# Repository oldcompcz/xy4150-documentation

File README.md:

# xy4150-documentation
Technical documentation about plotter XY 4150

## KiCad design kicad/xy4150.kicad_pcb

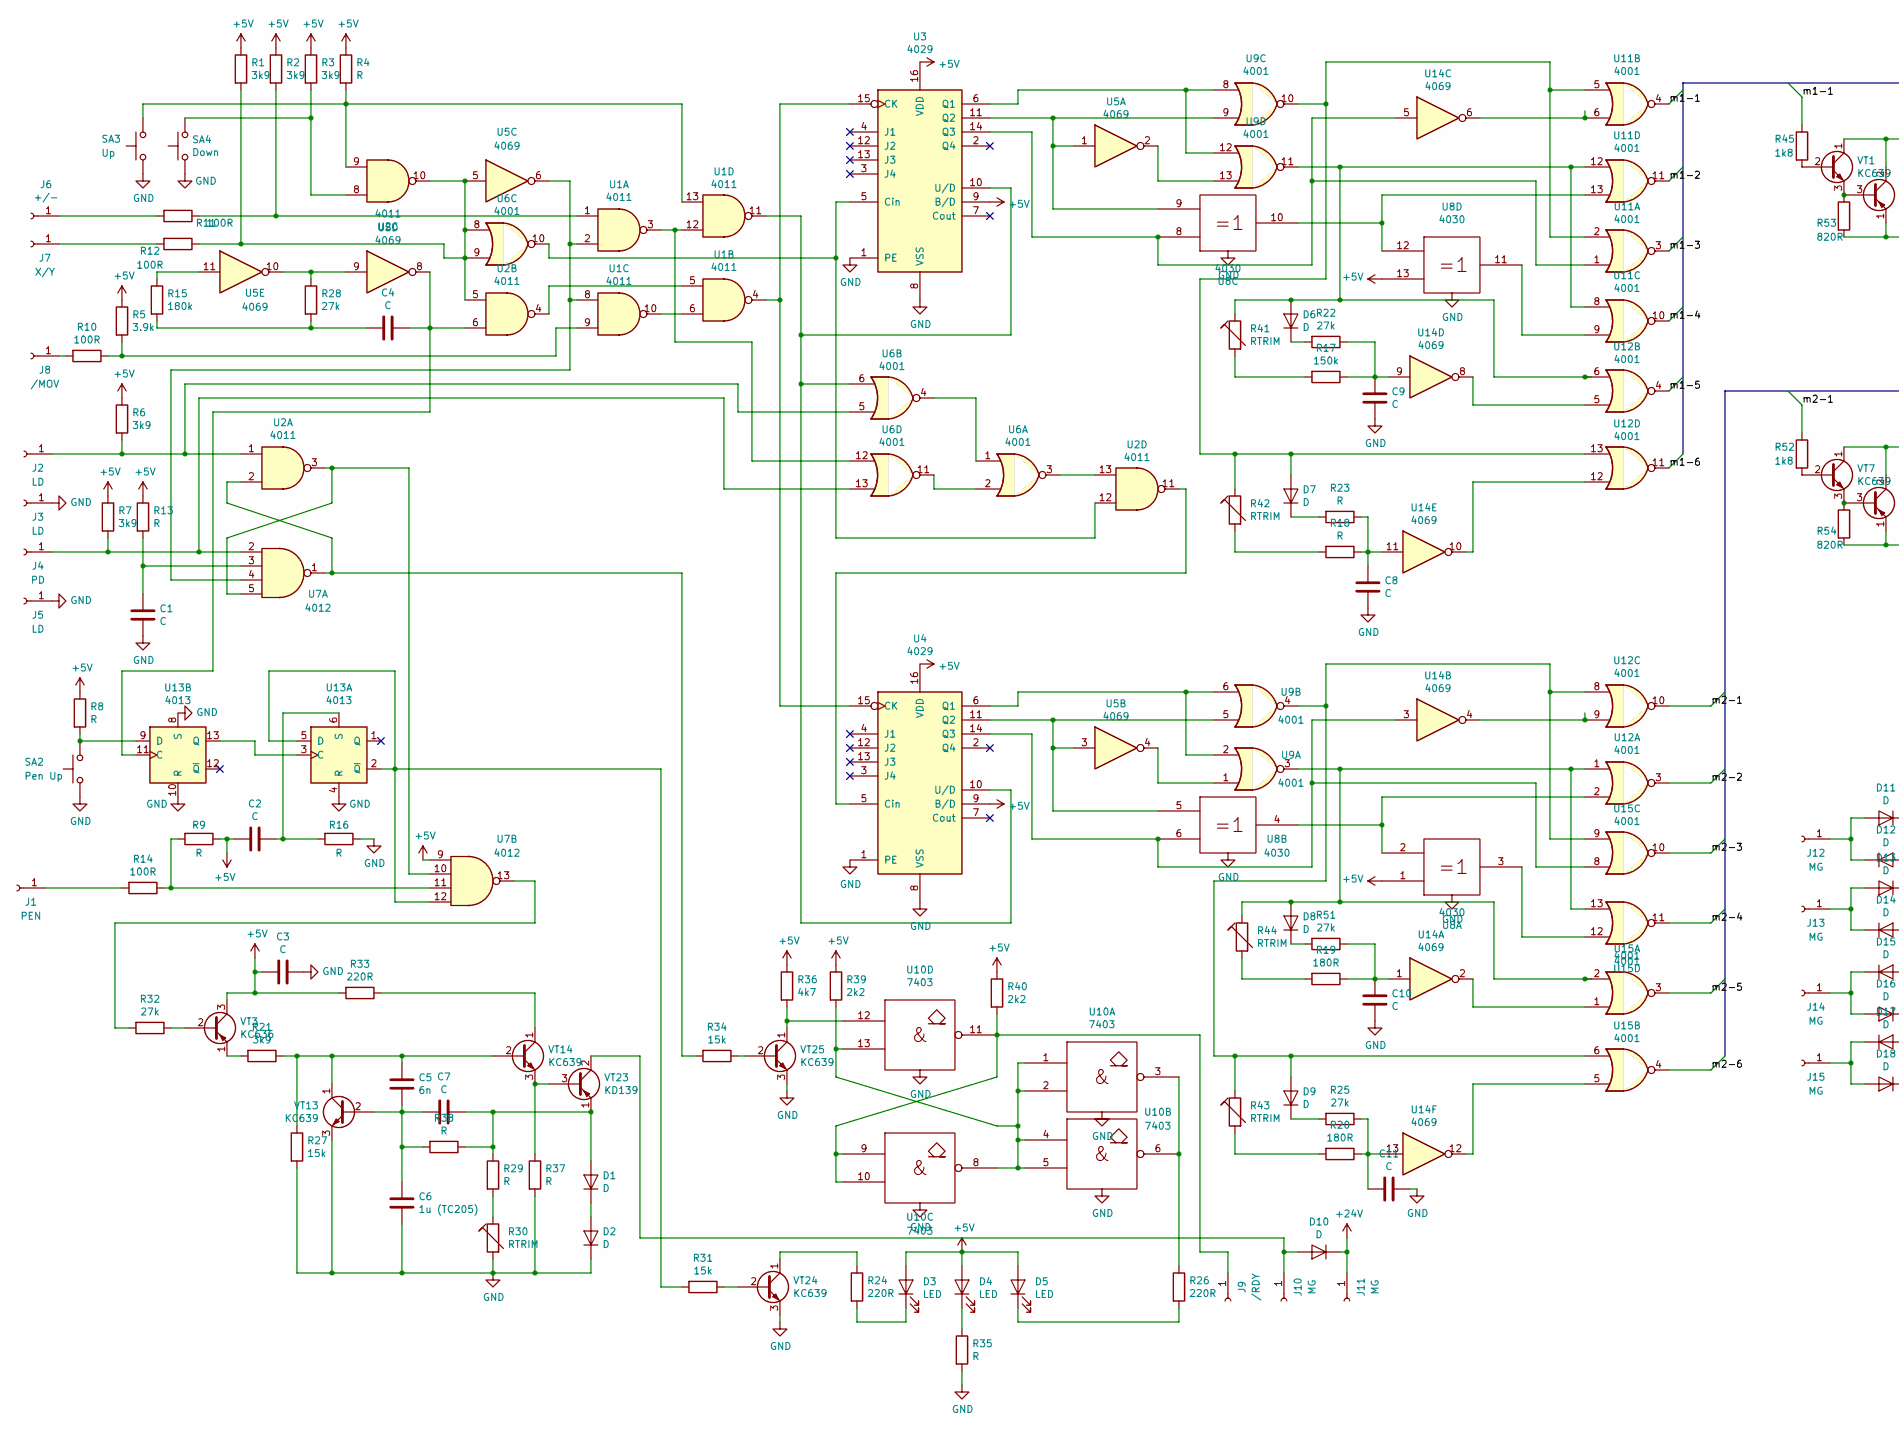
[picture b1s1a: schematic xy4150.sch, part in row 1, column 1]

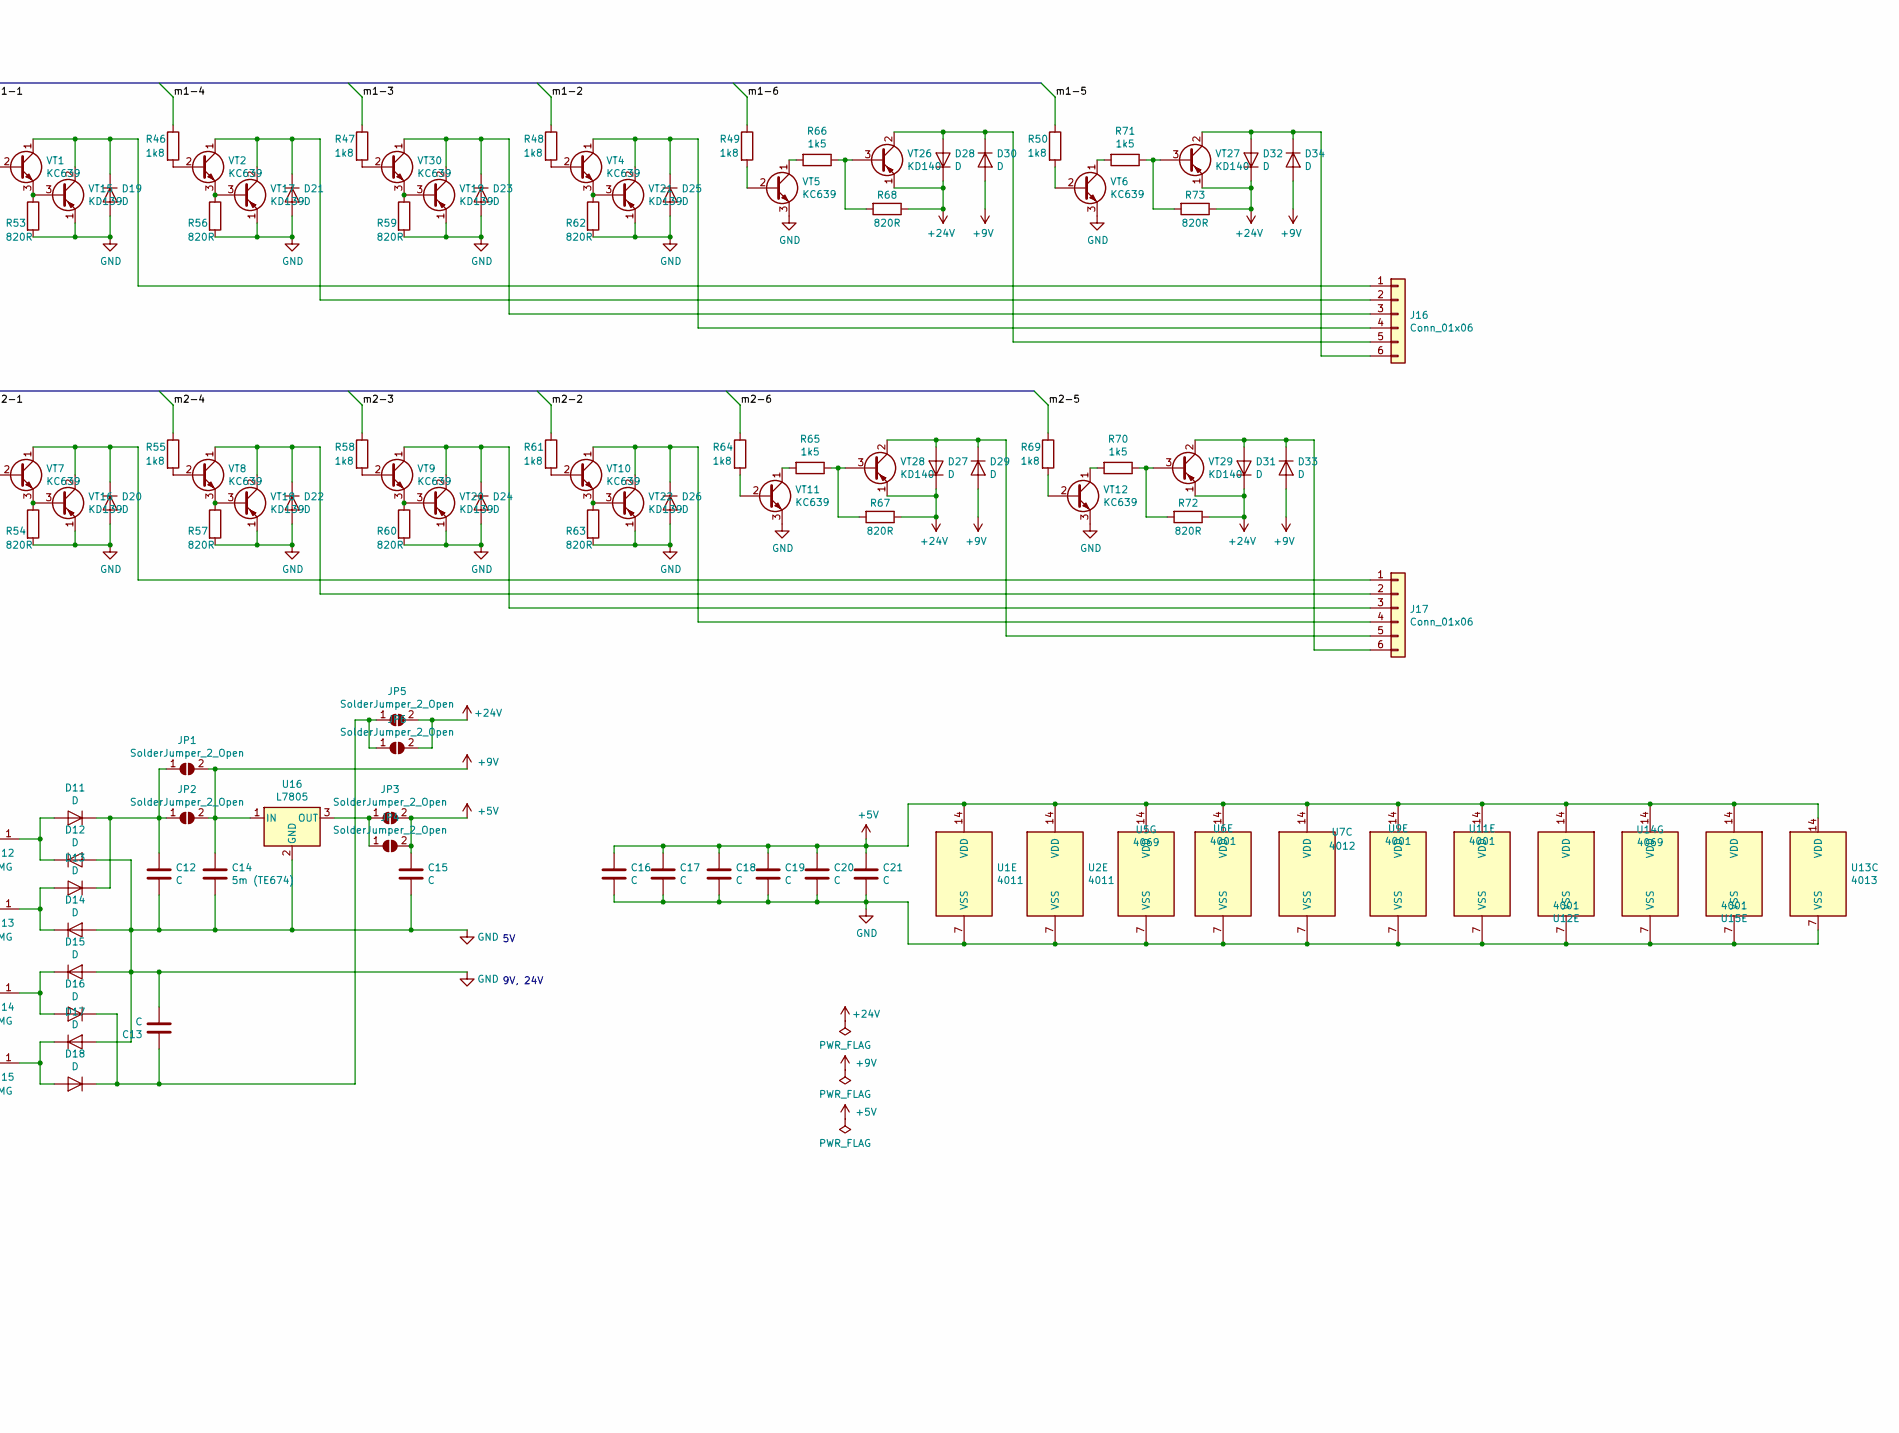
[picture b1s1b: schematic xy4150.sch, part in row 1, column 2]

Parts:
C1, C2, C3, C4, C7, C8, C9, C10, C11, C12, C15, C16, C17, C18, C19, C20, C21: C; C_Disc_D10.0mm_W2.5mm_P5.00mm
C5: 6n; C_Disc_D7.5mm_W2.5mm_P5.00mm
C6: 1u (TC205); C_Axial_L19.0mm_D9.5mm_P25.00mm_Horizontal
C13: C; TE-61x25
C14: 5m (TE674); TE-61x25
D1, D2, D6, D7, D8, D9, D10, D11, D12, D13, D14, D15, D16, D17, D18, D19, D20, D21, D22, D23, D24, D25, D26, D27, D28, D29, D30, D31, D32, D33, D34: D; D_DO-34_SOD68_P10.16mm_Horizontal
D3, D4, D5: LED; LED_Rectangular_W5.0mm_H2.0mm
J1: PEN; Pin_D0.7mm_L6.5mm_W1.8mm_FlatFork
J2, J3, J5: LD; Pin_D0.7mm_L6.5mm_W1.8mm_FlatFork
J4: PD; Pin_D0.7mm_L6.5mm_W1.8mm_FlatFork
J6: +/-; Pin_D0.7mm_L6.5mm_W1.8mm_FlatFork
J7: X/Y; Pin_D0.7mm_L6.5mm_W1.8mm_FlatFork
J8: /MOV; Pin_D0.7mm_L6.5mm_W1.8mm_FlatFork
J9: /RDY; Pin_D0.7mm_L6.5mm_W1.8mm_FlatFork
J10, J11, J12, J13, J14, J15: MG; Pin_D0.7mm_L6.5mm_W1.8mm_FlatFork
J16, J17: Conn_01x06; PinHeader_1x06_P1.00mm_Horizontal
JP1: SolderJumper_2_Open; SolderJumper-2_P1.3mm_Open_Pad1.0x1.5mm
JP2, JP3, JP4, JP5, JP6: SolderJumper_2_Open; SolderJumper-2_P1.3mm_Open_TrianglePad1.0x1.5mm
R1, R2, R3, R6, R7, R21: 3k9; R_Axial_DIN0207_L6.3mm_D2.5mm_P10.16mm_Horizontal
R4, R8, R9, R13, R16, R18, R23, R29, R35, R37, R38: R; R_Axial_DIN0207_L6.3mm_D2.5mm_P10.16mm_Horizontal
R5: 3.9k; R_Axial_DIN0207_L6.3mm_D2.5mm_P10.16mm_Horizontal
R10, R11, R12, R14: 100R; R_Axial_DIN0207_L6.3mm_D2.5mm_P10.16mm_Horizontal
R15: 180k; R_Axial_DIN0207_L6.3mm_D2.5mm_P10.16mm_Horizontal
R17: 150k; R_Axial_DIN0207_L6.3mm_D2.5mm_P10.16mm_Horizontal
R19, R20: 180R; R_Axial_DIN0207_L6.3mm_D2.5mm_P10.16mm_Horizontal
R22, R25, R28, R32, R51: 27k; R_Axial_DIN0207_L6.3mm_D2.5mm_P10.16mm_Horizontal
R24, R26, R33: 220R; R_Axial_DIN0207_L6.3mm_D2.5mm_P10.16mm_Horizontal
R27, R31, R34: 15k; R_Axial_DIN0207_L6.3mm_D2.5mm_P10.16mm_Horizontal
R30, R41, R42, R43, R44: RTRIM; R_Axial_DIN0207_L6.3mm_D2.5mm_P10.16mm_Horizontal
R36: 4k7; R_Axial_DIN0207_L6.3mm_D2.5mm_P10.16mm_Horizontal
R39, R40: 2k2; R_Axial_DIN0207_L6.3mm_D2.5mm_P10.16mm_Horizontal
R45, R46, R47, R48, R49, R50, R52, R55, R58, R61, R64, R69: 1k8; R_Axial_DIN0207_L6.3mm_D2.5mm_P10.16mm_Horizontal
R53, R54, R56, R57, R59, R60, R62, R63, R67, R68, R72, R73: 820R; R_Axial_DIN0207_L6.3mm_D2.5mm_P10.16mm_Horizontal
R65, R66, R70, R71: 1k5; R_Axial_DIN0207_L6.3mm_D2.5mm_P10.16mm_Horizontal
SA2: Pen Up; R_Axial_DIN0207_L6.3mm_D2.5mm_P10.16mm_Horizontal
SA3: Up; R_Axial_DIN0207_L6.3mm_D2.5mm_P10.16mm_Horizontal
SA4: Down; R_Axial_DIN0207_L6.3mm_D2.5mm_P10.16mm_Horizontal
U1, U2: 4011; DIP-14_W7.62mm
U3, U4: 4029; DIP-16_W7.62mm
U5, U14: 4069; DIP-14_W7.62mm
U6, U9, U11, U12, U15: 4001; DIP-14_W7.62mm
U7: 4012; DIP-14_W7.62mm
U8: 4030; DIP-14_W7.62mm
U10: 7403; DIP-14_W7.62mm
U13: 4013; DIP-14_W7.62mm
U16: L7805; TO-3
VT1, VT2, VT4, VT5, VT6, VT7, VT8, VT9, VT10, VT11, VT12, VT13, VT14, VT24, VT25, VT30: KC639; TO-92
VT3: KC636; TO-92
VT15, VT16, VT17, VT18, VT19, VT20, VT21, VT22, VT23: KD139; TO-126-3_Vertical
VT26, VT27, VT28, VT29: KD140; TO-126-3_Vertical

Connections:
+5V: C2.2, C3.2, C15.1, C16.1, C17.1, C18.1, C19.1, C20.1, C21.1, D3.2 (A), D4.2 (A), D5.2 (A), JP3.2 (B), JP4.2 (B), R1.1, R2.1, R3.1, R4.1, R5.1, R6.1, R7.1, R8.1, R9.1, R13.1, R33.2, R36.1, R39.1, R40.1, U1.14 (VDD), U2.14 (VDD), U3.9 (B/D), U3.16 (VDD), U4.9 (B/D), U4.16 (VDD), U5.14 (VDD), U6.14 (VDD), U7.9, U7.14 (VDD), U8.1, U8.13, U9.14 (VDD), U11.14 (VDD), U12.14 (VDD), U13.14 (VDD), U14.14 (VDD), U15.14 (VDD), VT3.3
+9V: C14.1, D29.2 (A), D30.2 (A), D33.2 (A), D34.2 (A), JP1.2 (B), JP2.2 (B), U16.1 (IN)
+24V: D10.1 (K), D27.1 (K), D28.1 (K), D31.1 (K), D32.1 (K), J11.1, JP5.2 (B), JP6.2 (B), R67.1, R68.1, R72.1, R73.1, VT26.1, VT27.1, VT28.1, VT29.1
/m1-1: R45.1, U11.4
/m1-2: R48.1, U11.11
/m1-3: R47.1, U11.3
/m1-4: R46.1, U11.10
/m1-5: R50.1, U12.4
/m1-6: R49.1, U12.11
/m2-1: R52.1, U12.10
/m2-2: R61.1, U12.3
/m2-3: R58.1, U15.10
/m2-4: R55.1, U15.11
/m2-5: R69.1, U15.3
/m2-6: R64.1, U15.4
GND: C1.2, C3.1, C6.2, C8.2, C9.2, C10.2, C11.1, C12.2, C13.2, C14.2, C15.2, C16.2, C17.2, C18.2, C19.2, C20.2, C21.2, D2.1 (K), D12.2 (A), D14.2 (A), D15.2 (A), D17.2 (A), D19.2 (A), D20.2 (A), D21.2 (A), D22.2 (A), D23.2 (A), D24.2 (A), D25.2 (A), D26.2 (A), J3.1, J5.1, R16.1, R27.2, R30.2, R35.2, R37.2, R53.2, R54.2, R56.2, R57.2, R59.2, R60.2, R62.2, R63.2, SA2.1, SA3.1, SA4.1, U1.7 (VSS), U2.7 (VSS), U3.1 (PE), U3.8 (VSS), U4.1 (PE), U4.8 (VSS), U5.7 (VSS), U6.7 (VSS), U7.7 (VSS), U8.7 (Vss), U8.14 (Vdd), U9.7 (VSS), U10.7 (GND), U11.7 (VSS), U12.7 (VSS), U13.4 (R), U13.7 (VSS), U13.8 (S), U13.10 (R), U14.7 (VSS), U15.7 (VSS), U16.2 (GND), VT5.3, VT6.3, VT11.3, VT12.3, VT13.3, VT15.1, VT16.1, VT17.1, VT18.1, VT19.1, VT20.1, VT21.1, VT22.1, VT24.3, VT25.3
unnamed: C1.1, R13.2, U7.3
unnamed: C2.1, R16.2, U13.6 (S)
unnamed: C4.1, U2.6, U5.8, U13.11 (C)
unnamed: C4.2, R15.2, R28.2
unnamed: C5.1, R21.1, R27.1, VT13.1, VT14.2
unnamed: C5.2, C6.1, C7.1, R38.2, VT13.2
unnamed: C7.2, D1.2 (A), R29.1, R38.1, VT23.1
unnamed: C8.1, R18.1, R23.1, U14.11
unnamed: C9.1, R17.1, R22.1, U14.9
unnamed: C10.1, R19.1, R51.1, U14.1
unnamed: C11.2, R20.1, R25.1, U14.13
unnamed: C12.1, D11.1 (K), D13.1 (K), JP1.1 (A), JP2.1 (A)
unnamed: C13.1, D16.1 (K), D18.1 (K), JP5.1 (A), JP6.1 (A)
unnamed: D1.1 (K), D2.2 (A)
unnamed: D3.1 (K), R24.2
unnamed: D4.1 (K), R35.1
unnamed: D5.1 (K), R26.2
unnamed: D6.1 (K), R22.2
unnamed: D6.2 (A), R41.1, U9.11, U11.8, U11.12, U12.6
unnamed: D7.1 (K), R23.2
unnamed: D7.2 (A), R42.1, U9.10, U11.2, U11.5, U12.13
unnamed: D8.1 (K), R51.2
unnamed: D8.2 (A), R44.1, U9.3, U12.1, U15.2, U15.13
unnamed: D9.1 (K), R25.2
unnamed: D9.2 (A), R43.1, U9.4, U12.8, U15.6, U15.9
unnamed: D10.2 (A), J10.1, VT23.2
unnamed: D11.2 (A), D12.1 (K), J12.1
unnamed: D13.2 (A), D14.1 (K), J13.1
unnamed: D15.1 (K), D16.2 (A), J14.1
unnamed: D17.1 (K), D18.2 (A), J15.1
unnamed: D19.1 (K), J16.1, VT1.1, VT15.2
unnamed: D20.1 (K), J17.1, VT7.1, VT16.2
unnamed: D21.1 (K), J16.2, VT2.1, VT17.2
unnamed: D22.1 (K), J17.2, VT8.1, VT18.2
unnamed: D23.1 (K), J16.3, VT19.2, VT30.1
unnamed: D24.1 (K), J17.3, VT9.1, VT20.2
unnamed: D25.1 (K), J16.4, VT4.1, VT21.2
unnamed: D26.1 (K), J17.4, VT10.1, VT22.2
unnamed: D27.2 (A), D29.1 (K), J17.5, VT28.2
unnamed: D28.2 (A), D30.1 (K), J16.5, VT26.2
unnamed: D31.2 (A), D33.1 (K), J17.6, VT29.2
unnamed: D32.2 (A), D34.1 (K), J16.6, VT27.2
unnamed: J1.1, R14.2
unnamed: J2.1, R6.2, U2.1, U6.5
unnamed: J4.1, R7.2, U6.13, U7.2
unnamed: J6.1, R11.2
unnamed: J7.1, R12.2
unnamed: J8.1, R10.2
unnamed: J9.1, R40.2, U10.9, U10.10, U10.11
unnamed: JP3.1 (A), JP4.1 (A), U16.3 (OUT)
unnamed: R1.2, R12.1, U2.5, U2.10, U5.5, U6.8, U6.9
unnamed: R3.2, SA4.2, U2.8
unnamed: R4.2, SA3.2, U1.13, U2.9
unnamed: R8.2, SA2.2, U13.9 (D)
unnamed: R5.2, R10.1, U1.9
unnamed: R2.2, R11.1, U1.1
unnamed: R9.2, R14.1, U7.11
unnamed: R15.1, U5.11
unnamed: R17.2, R41.2
unnamed: R18.2, R42.2
unnamed: R19.2, R44.2
unnamed: R20.2, R43.2
unnamed: R21.2, VT3.1
unnamed: R24.1, VT24.1
unnamed: R26.1, U10.3, U10.6
unnamed: R28.1, U5.9, U5.10
unnamed: R29.2, R30.1
unnamed: R31.1, VT24.2
unnamed: R31.2, U7.12, U13.2 (~Q), U13.5 (D)
unnamed: R32.1, VT3.2
unnamed: R32.2, U7.13
unnamed: R33.1, VT14.1
unnamed: R34.1, VT25.2
unnamed: R34.2, U2.2, U7.1
unnamed: R36.2, U10.12, VT25.1
unnamed: R37.1, VT14.3, VT23.3
unnamed: R39.2, U10.1, U10.2, U10.4, U10.5, U10.8, U10.13
unnamed: R45.2, VT1.2
unnamed: R46.2, VT2.2
unnamed: R47.2, VT30.2
unnamed: R48.2, VT4.2
unnamed: R49.2, VT5.2
unnamed: R50.2, VT6.2
unnamed: R52.2, VT7.2
unnamed: R53.1, VT1.3, VT15.3
unnamed: R54.1, VT7.3, VT16.3
unnamed: R55.2, VT8.2
unnamed: R56.1, VT2.3, VT17.3
unnamed: R57.1, VT8.3, VT18.3
unnamed: R58.2, VT9.2
unnamed: R59.1, VT19.3, VT30.3
unnamed: R60.1, VT9.3, VT20.3
unnamed: R61.2, VT10.2
unnamed: R62.1, VT4.3, VT21.3
unnamed: R63.1, VT10.3, VT22.3
unnamed: R64.2, VT11.2
unnamed: R65.1, R67.2, VT28.3
unnamed: R65.2, VT11.1
unnamed: R66.1, R68.2, VT26.3
unnamed: R66.2, VT5.1
unnamed: R69.2, VT12.2
unnamed: R70.1, R72.2, VT29.3
unnamed: R70.2, VT12.1
unnamed: R71.1, R73.2, VT27.3
unnamed: R71.2, VT6.1
unnamed: U1.2, U1.8, U5.6, U7.4
unnamed: U1.4, U3.15 (CK), U4.15 (CK)
unnamed: U1.5, U2.4
unnamed: U1.6, U1.10
unnamed: U1.11, U3.10 (U/D), U4.10 (U/D), U6.6
unnamed: U1.3, U1.12, U6.12
unnamed: U2.3, U7.5, U7.10
unnamed: U2.11, U4.5 (Cin)
unnamed: U2.12, U3.5 (Cin), U6.10
unnamed: U2.13, U6.3
unnamed: U3.6 (Q1), U9.8, U9.12
unnamed: U3.11 (Q2), U5.1, U8.9, U9.9
unnamed: U4.6 (Q1), U9.2, U9.6
unnamed: U4.11 (Q2), U5.3, U8.5, U9.5
unnamed: U5.2, U9.13
unnamed: U5.4, U9.1
unnamed: U6.1, U6.4
unnamed: U6.2, U6.11
unnamed: U3.14 (Q3), U8.8, U11.1, U14.5
unnamed: U11.6, U14.6
unnamed: U8.11, U11.9
unnamed: U8.10, U8.12, U11.13
unnamed: U8.2, U8.4, U12.2
unnamed: U12.5, U14.8
unnamed: U12.9, U14.4
unnamed: U12.12, U14.10
unnamed: U13.3 (C), U13.13 (Q)
unnamed: U14.2, U15.1
unnamed: U4.14 (Q3), U8.6, U14.3, U15.8
unnamed: U14.12, U15.5
unnamed: U8.3, U15.12

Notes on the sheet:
9V, 24V

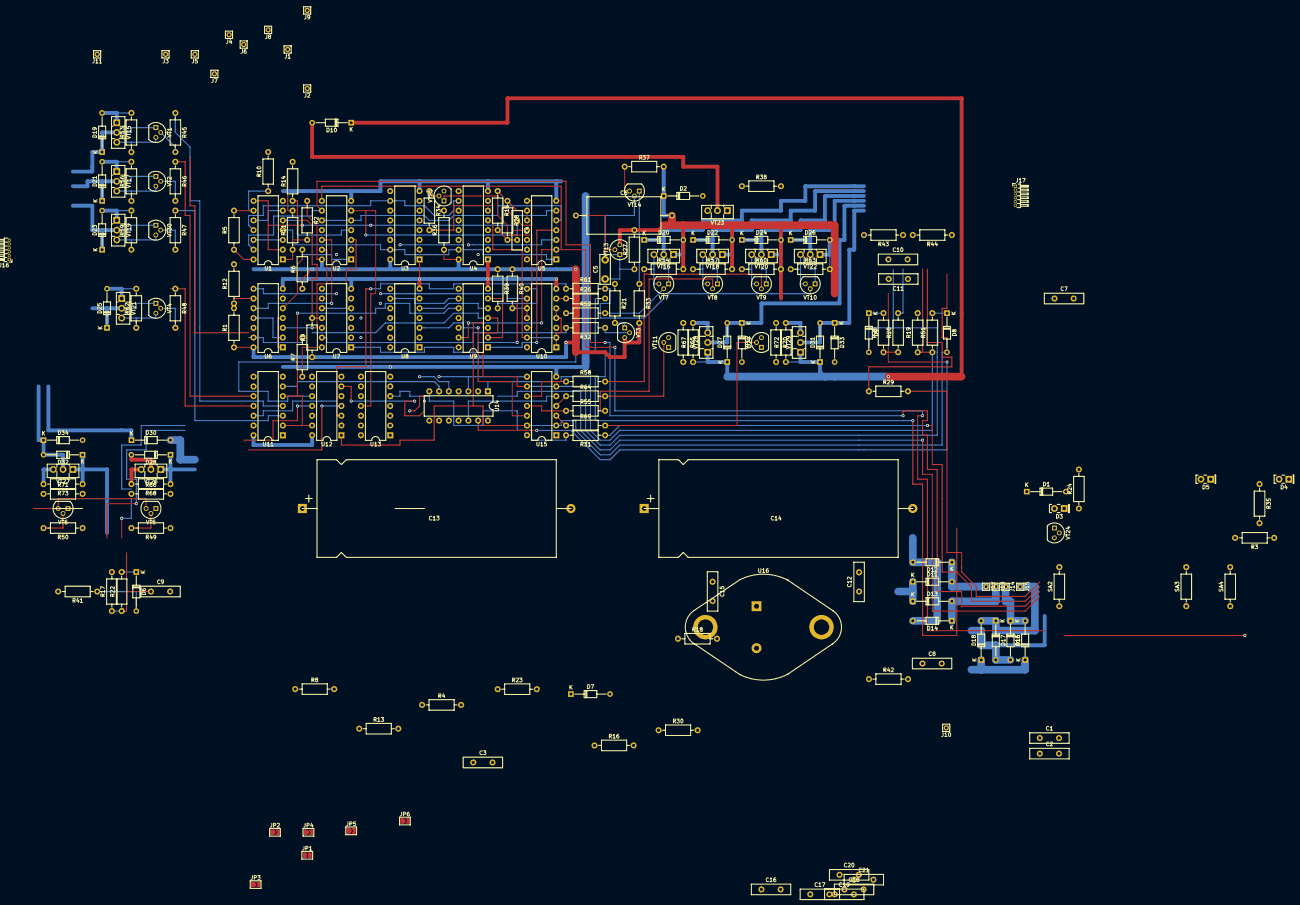
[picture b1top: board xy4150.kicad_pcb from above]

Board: 2 copper layers, 200 parts (0 on the bottom side), 152 nets.

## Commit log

2019-09-16 add some documentation
2019-09-18 add photos of wires order
2019-09-19 add svg with aligned pcb photos in layers
2019-09-29 add working version of the schematics
2019-09-29 schema fixes
2019-09-29 component library
2019-09-30 start with pcb
2019-10-01 update pcb
2019-10-15 update pcb and schema
